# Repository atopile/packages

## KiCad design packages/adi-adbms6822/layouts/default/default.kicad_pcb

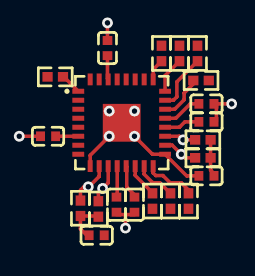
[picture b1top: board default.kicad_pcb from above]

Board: 2 copper layers, 21 parts (0 on the bottom side), 18 nets.

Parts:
C1, C2, C3, C4, C5, C6: 1e-06F; C0402
C7, C8: 1.0000000000000001e-07F; C0402
R1, R2: 10000.0Ω; R0402
R3, R4, R5, R6, R7, R8: 10.0Ω; R0402
R9, R10, R11, R12: 49.9Ω; R0402
U1: HVQFN-32_L5.0-W5.0-P0.50-TL-EP2.1

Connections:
18_N: R12.2, U1.18
19_P: R11.1, U1.19
IM_N: R10.2, U1.10
IP_P: R9.1, U1.11
MSTR_1_CONFIG: R1.1, U1.1
MSTR_2_CONFIG: R2.1, U1.25
PHAPOL_1_CONFIG: R3.1, U1.14
PHAPOL_2_CONFIG: R4.1, U1.22
RTO_1_CONFIG: R7.1, U1.15
RTO_2_CONFIG: R8.1, U1.23
XCVRMD_1_CONFIG: R5.1, U1.16
XCVRMD_2_CONFIG: R6.1, U1.24
bypass_capacitors[1]-power-hv: C1.1, C2.1, R1.2, R2.2, R3.2, R4.2, U1.6, U1.30
bypass_capacitors[3]-power-hv: C3.1, C4.1, U1.12, U1.20
bypass_capacitors[5]-power-hv: C5.1, C6.1, U1.13, U1.21
isoSPI_dc_bias_caps[0]-power-hv: C7.1, R9.2, R10.1
isoSPI_dc_bias_caps[1]-power-hv: C8.1, R11.2, R12.1
lv: C1.2, C2.2, C3.2, C4.2, C5.2, C6.2, C7.2, C8.2, R5.2, R6.2, R7.2, R8.2, U1.9, U1.17, U1.33

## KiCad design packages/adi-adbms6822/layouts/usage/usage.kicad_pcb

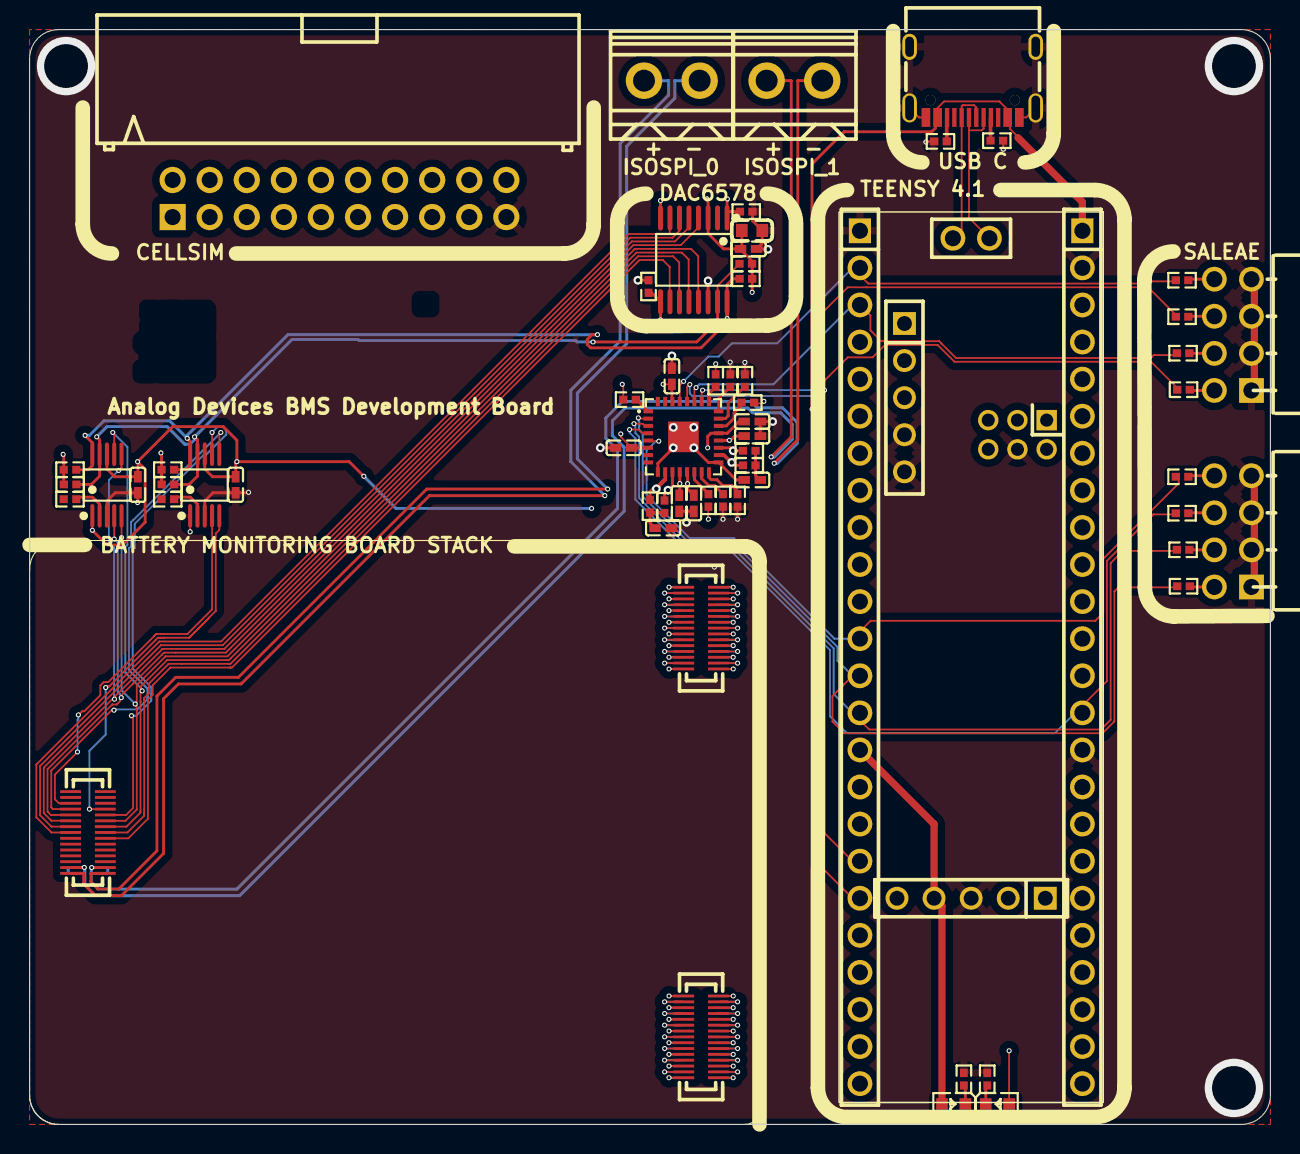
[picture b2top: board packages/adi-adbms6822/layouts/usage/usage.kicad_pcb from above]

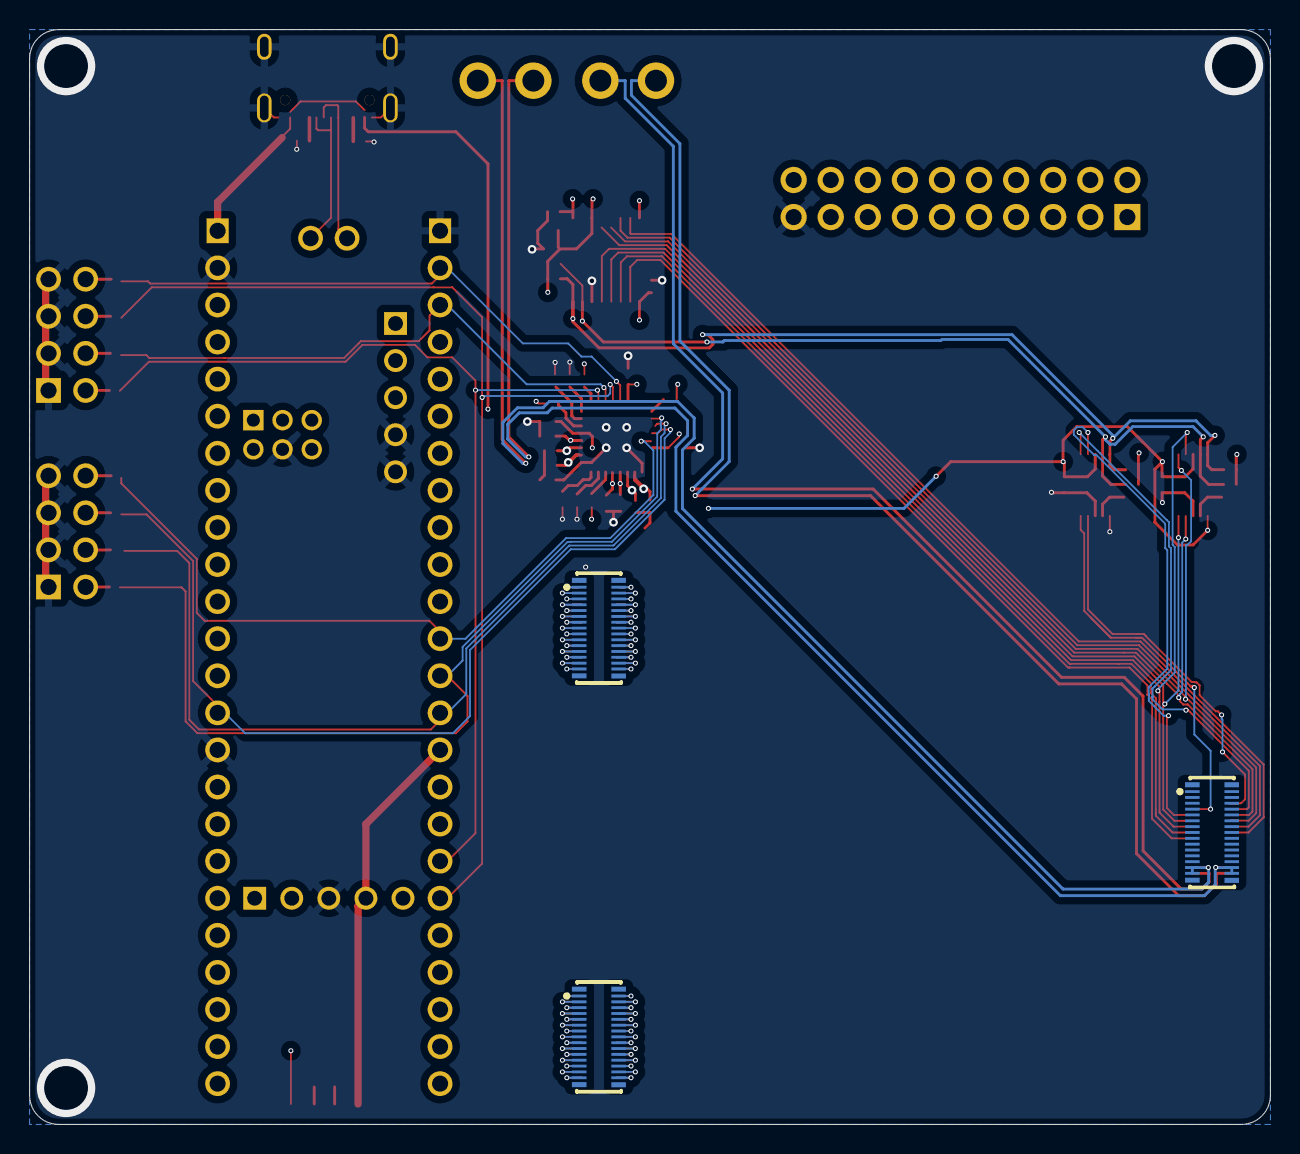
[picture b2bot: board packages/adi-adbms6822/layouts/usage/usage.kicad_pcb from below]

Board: 4 copper layers, 85.0 x 75.0 mm, 71 parts (3 on the bottom side), 97 nets.

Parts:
C1, C2, C3, C4, C5, C6: 1µF ±10% 25V X5R; C0402
C7: 10µF ±20% 6.3V X5R; C0603
C8, C9, C10, C11, C12: 100nF ±10% 16V X7R; C0402
CN1: CONN-TH_2P-P2.50_YZ88715155P-02025-01
CN2: IDC-TH_Z-231012820106
CN3, CN5, CN7: CONN-SMD_DF40C-30DP-0.4V-51
CN4, CN6, CN8: CONN-SMD_30P-P0.40_DF40HC-3.0-30DS-0.4V-51
LED1, LED2: LED0603-RD
R1, R2, R19, R20, R23, R24, R29, R30, R31, R32, R33, R34: 10kΩ ±1% 62.5mW; R0402
R3, R4, R5, R6: 10Ω ±1% 62.5mW; R0402
R7, R8: 0Ω 62.5mW; R0402
R9, R10, R11, R12, R13, R14, R15, R16: 1kΩ ±1% 62.5mW; R0402
R17, R18, R21, R22: 4.7kΩ ±1% 62.5mW; R0402
R25, R26, R27, R28: 49.9Ω ±1% 62.5mW; R0402
U1: HVQFN-32_L5.0-W5.0-P0.50-TL-EP2.1
U2, U3: HDR-TH_8P-P2.54-H-F-R2-C4-W8.5
U4: HDR-TH_6P-P2.00-V-F-R2-C3-S2.00
U5, U8: HDR-TH_5P-P2.54-V-F
U6, U7: HDR-TH_24P-P2.54-V-F
U9: PJRC_Teensy_4_1
U10: TSSOP-16_L5.0-W4.4-P0.65-LS6.4-BL
U11, U12: CONN-TH_2P-P3.81_DB125-3.81-2P-BK-S
U13, U14: MSOP-10_L3.0-W3.0-P0.50-LS5.0-BL
USB1: USB-C-SMD_KH-TYPE-C-16P

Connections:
A5: R17.1, USB1.A5
AIN0: CN8.6, U13.4
AIN1: CN8.7, U13.5
AIN2: CN8.8, U13.6
AIN3: CN8.9, U13.7
B5: R18.1, USB1.B5
CELL0: CN2.18, CN3.2, CN4.2, CN5.2, CN6.2
CELL1: CN2.17, CN3.3, CN4.3, CN5.3, CN6.3
CELL2: CN2.16, CN3.4, CN4.4, CN5.4, CN6.4
CELL3: CN2.15, CN3.5, CN4.5, CN5.5, CN6.5
CELL4: CN2.14, CN3.6, CN4.6, CN5.6, CN6.6
CELL5: CN2.13, CN3.7, CN4.7, CN5.7, CN6.7
CELL6: CN2.12, CN3.8, CN4.8, CN5.8, CN6.8
CELL7: CN2.11, CN3.9, CN4.9, CN5.9, CN6.9
CELL8: CN2.10, CN3.10, CN4.10, CN5.10, CN6.10
CELL9: CN2.9, CN3.11, CN4.11, CN5.11, CN6.11
CELL10: CN2.8, CN3.12, CN4.12, CN5.12, CN6.12
CELL11: CN2.7, CN3.13, CN4.13, CN5.13, CN6.13
CELL12: CN2.6, CN3.14, CN4.14, CN5.14, CN6.14
CELL13: CN2.5, CN3.15, CN4.15, CN5.15, CN6.15
CELL14: CN2.4, CN3.16, CN4.16, CN5.16, CN6.16
CELL15: CN2.3, CN3.17, CN4.17, CN5.17, CN6.17
CELL16: CN2.2, CN3.18, CN4.18, CN5.18, CN6.18
GND: C1.2, C2.2, C3.2, C4.2, C5.2, C6.2, C7.2, C8.2, C9.2, C10.2, C11.2, C12.2, CN2.19, CN3.1, CN4.1, CN5.1, CN6.1, R5.2, R6.2, R7.2, R8.2, R17.2, R18.2, R19.2, R20.2, R23.2, R24.2, U1.9, U1.17, U1.33, U2.1, U2.3, U2.5, U2.7, U3.1, U3.3, U3.5, U3.7, U4.4, U5.3, U6.1, U7.2, U7.15, U8.4, U8.5, U10.14, U13.1, U13.3, U14.3, USB1.1, USB1.2, USB1.3, USB1.4, USB1.A1, USB1.A12, USB1.B1, USB1.B12
ISO0_N: CN8.29, R26.2, U1.10, U11.2
ISO0_P: CN8.30, R25.1, U1.11, U11.1
ISO1_N: CN7.27, CN7.29, CN8.27, R28.2, U1.18, U12.2
ISO1_P: CN7.28, CN7.30, CN8.28, R27.1, U1.19, U12.1
MSTR_1_CONFIG: R1.1, U1.1
MSTR_2_CONFIG: R2.1, U1.25
PHAPOL_1_CONFIG: R3.1, U1.14
PHAPOL_2_CONFIG: R4.1, U1.22
RTO_1_CONFIG: R7.1, U1.15
RTO_2_CONFIG: R8.1, U1.23
XCVRMD_1_CONFIG: R5.1, U1.16
XCVRMD_2_CONFIG: R6.1, U1.24
adcs[0]-alert_ready-ALERT_RDY: R29.1, U13.2
adcs[1]-alert_ready-ALERT_RDY: R32.1, U14.2
cell_power_down-_19: CN3.19, CN4.19
cell_power_down-_20: CN3.20, CN4.20
cell_power_down-_21: CN3.21, CN4.21
cell_power_down-_22: CN3.22, CN4.22
cell_power_down-_23: CN3.23, CN4.23
cell_power_down-_24: CN3.24, CN4.24
cell_power_down-_25: CN3.25, CN4.25
cell_power_down-_26: CN3.26, CN4.26
cell_power_down-_27: CN3.27, CN4.27
cell_power_down-_28: CN3.28, CN4.28
cell_power_down-_29: CN3.29, CN4.29
cell_sense_down-_19: CN5.19, CN6.19
cell_sense_down-_20: CN5.20, CN6.20
cell_sense_down-_21: CN5.21, CN6.21
cell_sense_down-_22: CN5.22, CN6.22
cell_sense_down-_23: CN5.23, CN6.23
cell_sense_down-_24: CN5.24, CN6.24
cell_sense_down-_25: CN5.25, CN6.25
cell_sense_down-_26: CN5.26, CN6.26
cell_sense_down-_27: CN5.27, CN6.27
cell_sense_down-_28: CN5.28, CN6.28
cell_sense_down-_29: CN5.29, CN6.29
footprint-_2-0: R9.2, U2.2
footprint-_2-1: R13.2, U3.2
footprint-_4-0: R10.2, U2.4
footprint-_4-1: R14.2, U3.4
footprint-_6-0: R11.2, U2.6
footprint-_6-1: R15.2, U3.6
footprint-_8-0: R12.2, U2.8
footprint-_8-1: R16.2, U3.8
footprint-cathode-0: LED1.1, R23.1
footprint-cathode-1: LED2.1, R24.1
gpio[10]-RX: R12.1, U1.5, U6.12
i2c[0]-SCL: R21.1, R30.1, R33.1, U7.8, U10.16, U13.10, U14.10
i2c[0]-SDA: R22.1, R31.1, R34.1, U7.9, U10.15, U13.9, U14.9
iso_1_termination_midpoint: C9.1, R25.2, R26.1
iso_2_termination_midpoint: C10.1, R27.2, R28.1
nCLR: R19.1, U6.4, U10.9
nLDAC: R20.1, U6.5, U10.1
outputs[0]: CN8.10, U10.4, U14.4
outputs[1]: CN8.11, U10.13, U14.5
outputs[2]: CN8.12, U10.5, U14.6
outputs[3]: CN8.13, U10.12, U14.7
outputs[4]: CN8.14, U10.6
outputs[5]: CN8.15, U10.11
outputs[6]: CN8.16, U10.7
outputs[7]: CN8.17, U10.10
power-anode: C5.1, C6.1, C11.1, C12.1, LED1.2, U1.13, U1.21, U7.1, U13.8, U14.1, U14.8, USB1.A4, USB1.A9, USB1.B4, USB1.B9
power_3v3-anode: C1.1, C2.1, C3.1, C4.1, C7.1, C8.1, LED2.2, R1.2, R2.2, R3.2, R4.2, R21.2, R22.2, R30.2, R31.2, R33.2, R34.2, U1.6, U1.12, U1.20, U1.30, U5.4, U6.15, U7.3, U10.3, U10.8
spi[0]-MISO: R10.1, U1.3, U6.14
spi[0]-MOSI: R9.1, U1.2, U6.13
spi[0]-SCLK: R11.1, U1.4, U7.14
spi[1]-MOSI: R13.1, U1.26, U6.18
spi[1]-SCLK: R15.1, U1.28, U6.19
stack_power-VCC: CN2.1, CN3.30, CN4.30, CN5.30, CN6.30
uart[0]-MISO: R14.1, U1.27, U6.3
uart[0]-RX: R16.1, U1.29, U6.2
usb2-USB_D_N: CN1.1, USB1.A7, USB1.B7
usb2-USB_D_P: CN1.2, USB1.A6, USB1.B6

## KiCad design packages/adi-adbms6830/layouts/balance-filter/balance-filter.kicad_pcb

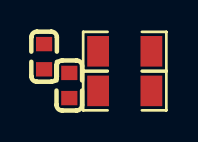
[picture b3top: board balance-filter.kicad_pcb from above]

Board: 2 copper layers, 4 parts (0 on the bottom side), 2 nets, no tracks yet.

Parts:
C1, C2: 10nF ±10% 50V X7R; C0603
R1, R2: 20Ω ±1% 250mW; R1206

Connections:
-gnd-0: C1.1, C2.2, R1.2
line: C2.1, R2.2

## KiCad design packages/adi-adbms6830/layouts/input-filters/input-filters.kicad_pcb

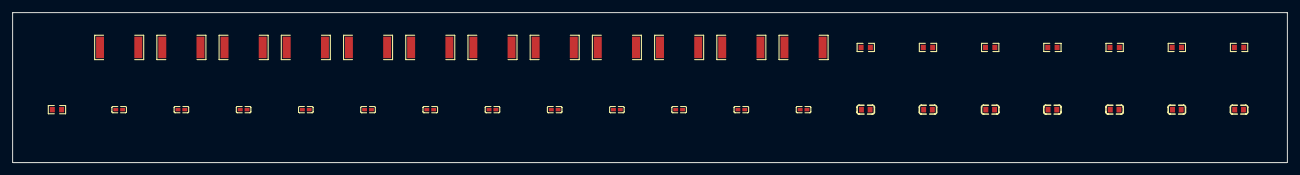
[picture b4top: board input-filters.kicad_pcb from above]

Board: 2 copper layers, 204.9 x 24.1 mm, 39 parts (0 on the bottom side), 26 nets, no tracks yet.

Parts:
C1, C2, C3, C4, C5, C6, C7, C8, C9, C10, C11, C12: 180nF ±10% 10V X5R; C0402
C13, C14, C15, C16, C17, C18, C19: 10nF ±10% 50V X7R; C0603
R1, R2, R3, R4, R5, R6, R7, R8, R9, R10, R11, R12: 11Ω ±1% 1W; R2512
R13, R15, R16, R17, R18, R19, R20: 200Ω ±1% 100mW; R0603
R14: 1kΩ ±1% 100mW; R0603

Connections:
-gnd-0: C1.1, C2.2, R1.2
-gnd-1: C2.1, C3.2, R2.2
-gnd-2: C1.2, C13.2, R1.1, R13.1
-gnd-3: R2.1, R3.1, R15.1
-gnd-4: C3.1, C4.2, R3.2
-gnd-5: C4.1, C5.2, R4.2
-gnd-6: R4.1, R5.1, R16.1
-gnd-7: C5.1, C6.2, R5.2
-gnd-8: C6.1, C7.2, R6.2
-gnd-9: R6.1, R7.1, R17.1
-gnd-10: C7.1, C8.2, R7.2
-gnd-11: C8.1, C9.2, R8.2
-gnd-12: R8.1, R9.1, R18.1
-gnd-13: C9.1, C10.2, R9.2
-gnd-14: C10.1, C11.2, R10.2
-gnd-15: R10.1, R11.1, R19.1
-gnd-16: C11.1, C12.2, R11.2
-gnd-17: C13.1, C14.2, R13.2
-line-0: C12.1, R12.2
-line-2: C14.1, R15.2
-line-3: C15.1, R16.2
-line-4: C16.1, R17.2
-line-5: C17.1, R18.2
-line-6: C18.1, R19.2
-line-7: C19.1, R20.2
hv: R12.1, R14.2, R20.1

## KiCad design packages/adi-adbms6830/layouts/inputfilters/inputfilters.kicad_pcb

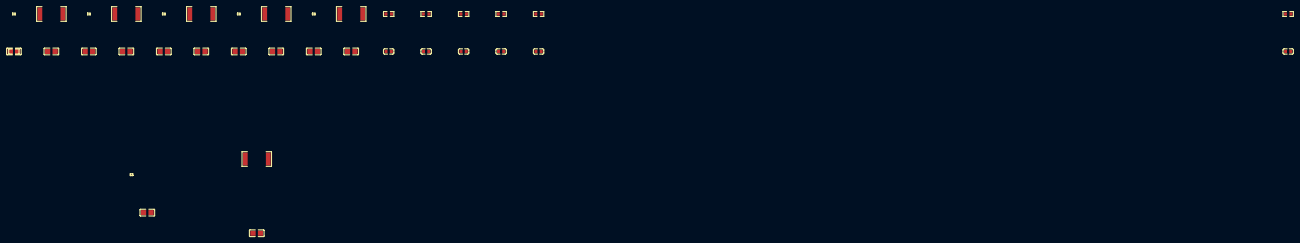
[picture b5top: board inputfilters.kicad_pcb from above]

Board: 2 copper layers, 37 parts (0 on the bottom side), 25 nets, no tracks yet.

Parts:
C1, C2, C3, C4, C5, C6, C7, C8, C9, C10, C11, C12: 200nF ±10% 50V X7R; C0805
C13, C14, C15, C16, C17, C34: 10nF ±10% 50V X7R; C0603
R1, R4, R6, R8, R10, R12: 11Ω ±1% 31.25mW; R01005
R2, R5, R7, R9, R11, R13: 11Ω ±1% 1W; R2512
R3: 1kΩ ±1% 100mW; R0603
R14, R15, R16, R17, R18, R35: 200Ω ±1% 100mW; R0603

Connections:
-gnd-0: C1.1, C2.2, R1.2
-gnd-1: C2.1, C3.2, R2.2
-gnd-2: C3.1, C4.2, R4.2
-gnd-3: C4.1, C5.2, R5.2
-gnd-5: C5.1, C6.2, R6.2
-gnd-6: C6.1, C7.2, R7.2
-gnd-8: C7.1, C8.2, R8.2
-gnd-9: C8.1, C9.2, R9.2
-gnd-11: C9.1, C10.2, R10.2
-gnd-12: C10.1, C11.2, R11.2
-gnd-14: C11.1, C12.2, R12.2
-hv-0: R2.1, R35.1
-hv-1: R5.1, R14.1
-hv-2: R7.1, R15.1
-hv-3: R9.1, R16.1
-hv-4: R11.1, R17.1
-hv-5: R3.2, R13.1, R18.1
-line-0: C12.1, R13.2
-line-2: C34.1, R35.2
-line-3: C13.1, R14.2
-line-4: C14.1, R15.2
-line-5: C15.1, R16.2
-line-6: C16.1, R17.2
-line-7: C17.1, R18.2
gnd-0: C1.2, R1.1

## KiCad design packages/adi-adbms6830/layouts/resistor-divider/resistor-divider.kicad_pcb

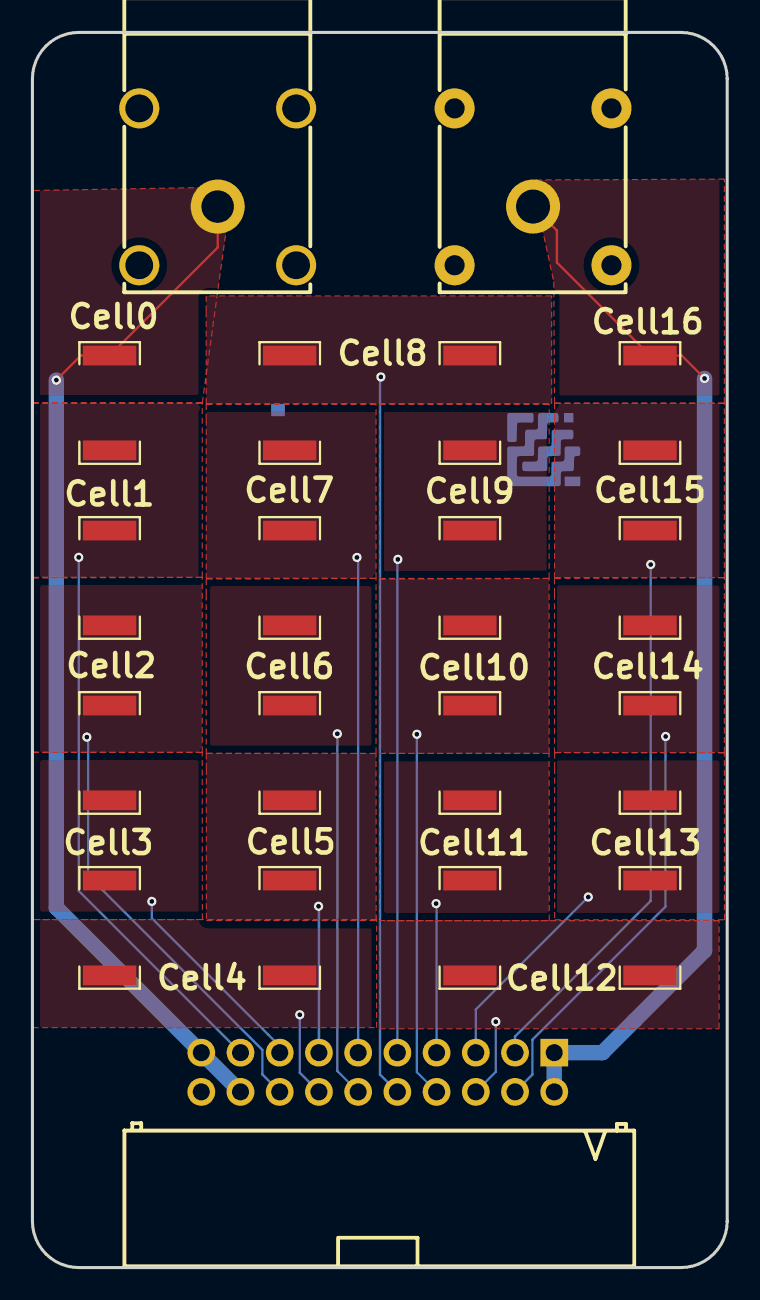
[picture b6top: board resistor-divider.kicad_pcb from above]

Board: 2 copper layers, 45.0 x 80.0 mm, 20 parts (1 on the bottom side), 17 nets.

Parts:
CN1: IDC-TH_Z-231012820106
J1: ANT-TH_L33.0-W12.0_BLACK
J2: ANT-TH_L33.0-W12.0_RED
LOGO1: atopile_Logo_25x6mm
R1, R2, R3, R4, R5, R6, R7, R8, R9, R10, R11, R12, R13, R14, R15, R16: 20Ω ±1% 1W; R2512

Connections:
CELL0: CN1.18, CN1.19, J1.5, R1.1
CELL1: CN1.17, R1.2, R2.1
CELL2: CN1.16, R2.2, R3.1
CELL3: CN1.15, R3.2, R4.1
CELL4: CN1.14, R4.2, R5.1
CELL5: CN1.13, R5.2, R6.1
CELL6: CN1.12, R6.2, R7.1
CELL7: CN1.11, R7.2, R8.1
CELL8: CN1.10, R8.2, R9.1
CELL9: CN1.9, R9.2, R10.1
CELL10: CN1.8, R10.2, R11.1
CELL11: CN1.7, R11.2, R12.1
CELL12: CN1.6, R12.2, R13.1
CELL13: CN1.5, R13.2, R14.1
CELL14: CN1.4, R14.2, R15.1
CELL15: CN1.3, R15.2, R16.1
CELL16: CN1.1, CN1.2, J2.5, R16.2

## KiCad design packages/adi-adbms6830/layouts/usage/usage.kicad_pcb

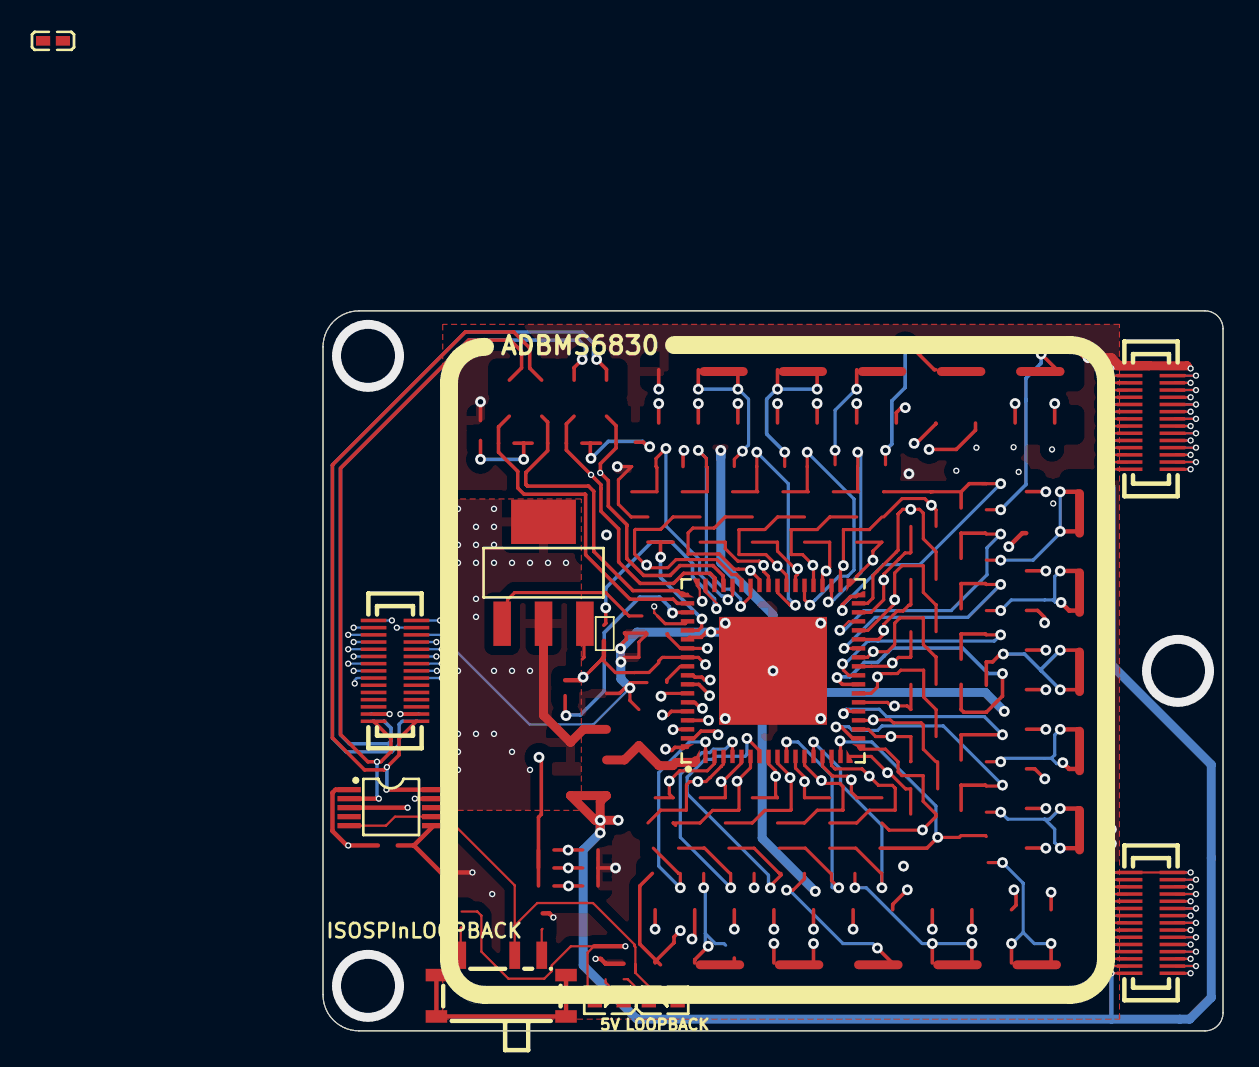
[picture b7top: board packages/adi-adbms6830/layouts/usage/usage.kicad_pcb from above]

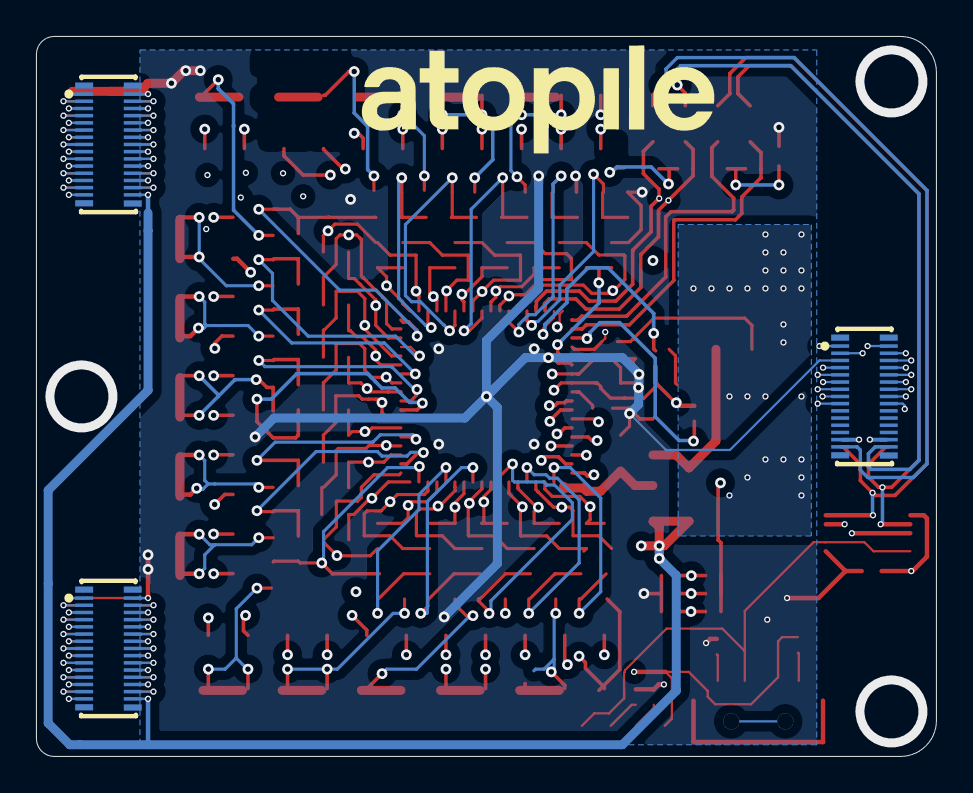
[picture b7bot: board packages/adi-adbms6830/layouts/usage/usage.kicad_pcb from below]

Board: 4 copper layers, 50.0 x 40.0 mm, 14 parts (4 on the bottom side), 64 nets.

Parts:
CN1, CN3, CN5: CONN-SMD_DF40C-30DP-0.4V-51
CN2, CN4, CN6: CONN-SMD_30P-P0.40_DF40HC-3.0-30DS-0.4V-51
L1: L0402
LED1, LED2: LED0603-RD
LOGO1: atopile_Logo_25x6mm
Q1: SOT-223-4_L6.5-W3.5-P2.30-LS7.0-BR
SW1: SW-TH_MSK12C02-HB-1
U1: VSSOP-10_L3.0-W3.0-P0.50-LS4.9-BL
U2: QFN-72_L10.0-W10.0-P0.50-BL-EP6.0_1

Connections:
19: CN1.19, CN2.19
20: CN1.20, CN2.20
21: CN1.21, CN2.21
22: CN1.22, CN2.22
23: CN1.23, CN2.23
24: CN1.24, CN2.24
25: CN1.25, CN2.25
26: CN1.26, CN2.26
27: CN1.27, CN2.27
28: CN1.28, CN2.28
29: CN1.29, CN2.29
DRIVE: CN5.9, U2.58
ISOMD: CN5.8, U2.53
ISOpass_N: CN5.27, CN6.27, U1.9
ISOpass_P: CN5.28, CN6.28, U1.3
MISO: CN5.2, U2.57
MOSI: CN5.1, U2.54
anode: LED2.2, SW1.2, U1.5, U1.7
cell_sense_down-19: CN3.19, CN4.19
cells[0]_N: CN1.1, CN1.2, CN2.1, CN2.2, CN3.1, CN3.2, CN4.1, CN4.2, CN5.5, U1.6, U2.60, U2.73
emitter: L1.1, Q1.3
gpios[3]-line: CN5.13, U2.69
gpios[4]-line: CN5.14, U2.68
gpios[5]-line: CN5.15, U2.67
gpios[6]-line: CN5.16, U2.66
gpios[7]-line: CN5.17, U2.65
gpios[8]-line: CN5.18, U2.64
iso_a_internal_N: CN5.4, U2.51
iso_a_internal_P: CN5.3, U2.52
iso_b_external_N: CN6.29, U1.10
iso_b_external_P: CN6.30, U1.2
line: CN5.10, U2.72
sbi-20: CN3.20, CN4.20
sbi-21: CN3.21, CN4.21
sbi-22: CN3.22, CN4.22
sbi-23: CN3.23, CN4.23
sbi-24: CN3.24, CN4.24
sbi-25: CN3.25, CN4.25
sbi-26: CN3.26, CN4.26
sbi-27: CN3.27, CN4.27
sbi-28: CN3.28, CN4.28
sbi-29: CN3.29, CN4.29
sense_filters[1]-cell_power-hv: CN1.3, CN2.3, CN3.3, CN4.3
sense_filters[2]-cell_power-hv: CN1.4, CN2.4, CN3.4, CN4.4
sense_filters[3]-cell_power-hv: CN1.5, CN2.5, CN3.5, CN4.5
sense_filters[4]-cell_power-hv: CN1.6, CN2.6, CN3.6, CN4.6
sense_filters[5]-cell_power-hv: CN1.7, CN2.7, CN3.7, CN4.7
sense_filters[6]-cell_power-hv: CN1.8, CN2.8, CN3.8, CN4.8
sense_filters[7]-cell_power-hv: CN1.9, CN2.9, CN3.9, CN4.9
sense_filters[8]-cell_power-hv: CN1.10, CN2.10, CN3.10, CN4.10
sense_filters[9]-cell_power-hv: CN1.12, CN2.12, CN3.12, CN4.12
sense_filters[9]-cell_power-hv-1: CN1.11, CN2.11, CN3.11, CN4.11
sense_filters[11]-cell_power-hv: CN1.13, CN2.13, CN3.13, CN4.13
sense_filters[12]-cell_power-hv: CN1.14, CN2.14, CN3.14, CN4.14
sense_filters[13]-cell_power-hv: CN1.15, CN2.15, CN3.15, CN4.15
sense_filters[14]-cell_power-hv: CN1.16, CN2.16, CN3.16, CN4.16
sense_filters[15]-cell_power-hv: CN1.17, CN2.17, CN3.17, CN4.17
sense_filters[15]-cell_power-hv-1: CN1.18, CN2.18, CN3.18, CN4.18
thermistors[1]-output-line: CN5.11, U2.71
thermistors[2]-output-line: CN5.12, U2.70
vbat-hv: CN1.30, CN2.30, CN3.30, CN4.30
vref2_cap-power-hv: CN5.7, U2.61
vreg_cap-power-anode: CN5.6, L1.2, LED1.2, U1.1, U2.62
vreg_input_c-power-hv: Q1.2, Q1.4
